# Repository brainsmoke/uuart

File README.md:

# Tiny USB-C to uart adapters using ch340n / ch340c / ch340b

* Green: simple 3v3 rx/tx (CH340N chip)
* Black: 3v3 rx/tx & reset circuit compatible with esptool (CH340C chip)
* Both: AP2112K-3.3 LDO

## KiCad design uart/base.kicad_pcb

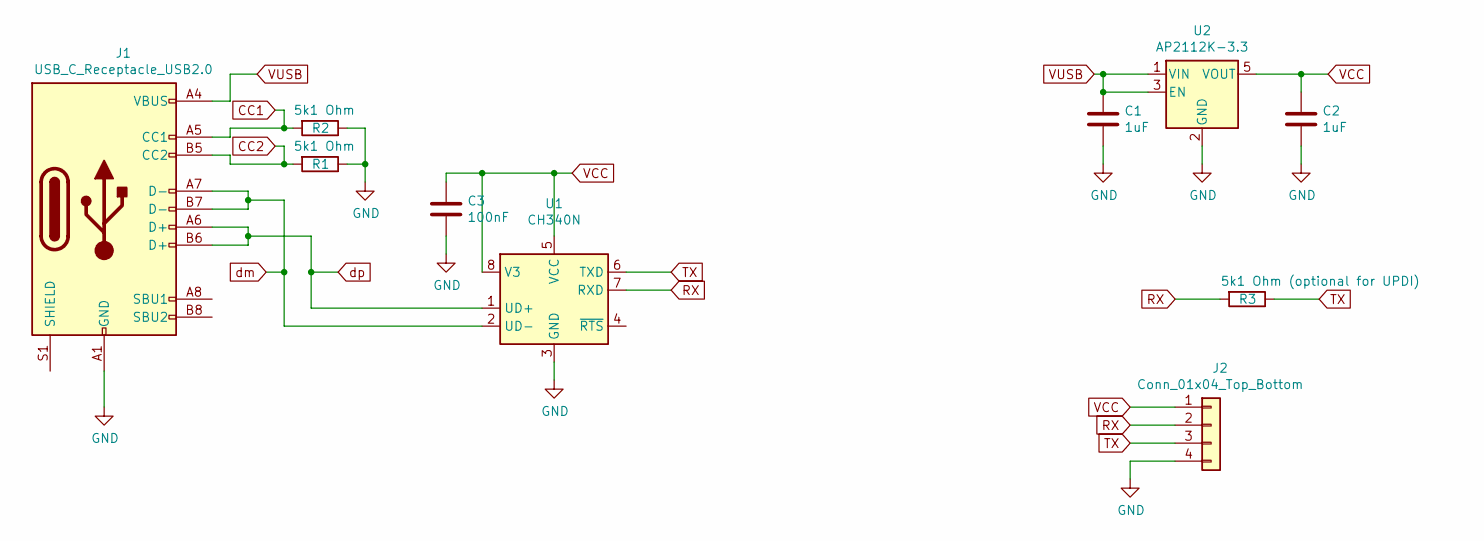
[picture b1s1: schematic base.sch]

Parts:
C1, C2: 1uF; C_0603_1608Metric
C3: 100nF; C_0603_1608Metric
J1: USB_C_Receptacle_USB2.0; USB_C_Receptacle_HRO_TYPE-C-31-M-12
J2: Conn_01x04_Top_Bottom; PinSocket_1x04_P2.54mm_Edge
R1, R2: 5k1 Ohm; R_0603_1608Metric
R3: 5k1 Ohm (optional for UPDI); R_0603_1608Metric
U1: CH340N; SOIC-8_3.9x4.9mm_P1.27mm
U2: AP2112K-3.3; SOT-23-5

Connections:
CC1: J1.A5 (CC1), R2.2
CC2: J1.B5 (CC2), R1.2
GND: C1.2, C2.2, C3.2, J1.A1 (GND), J1.A12 (GND), J1.B1 (GND), J1.B12 (GND), J2.4, R1.1, R2.1, U1.3 (GND), U2.2 (GND)
RX: J2.2, R3.2, U1.7 (RXD)
TX: J2.3, R3.1, U1.6 (TXD)
VCC: C2.1, C3.1, J2.1, U1.5 (VCC), U1.8 (V3), U2.5 (VOUT)
VUSB: C1.1, J1.A4 (VBUS), J1.A9 (VBUS), J1.B4 (VBUS), J1.B9 (VBUS), U2.1 (VIN), U2.3 (EN)
dm: J1.A7 (D-), J1.B7 (D-), U1.2 (UD-)
dp: J1.A6 (D+), J1.B6 (D+), U1.1 (UD+)

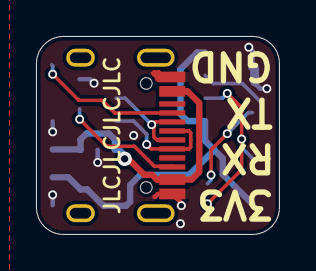
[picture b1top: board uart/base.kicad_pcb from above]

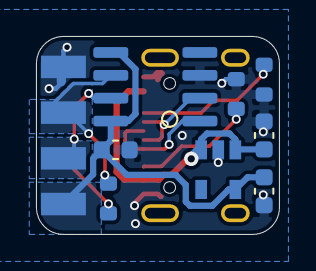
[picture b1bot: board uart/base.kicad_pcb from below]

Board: 2 copper layers, 13.5 x 11.0 mm, 10 parts (9 on the bottom side), 9 nets.

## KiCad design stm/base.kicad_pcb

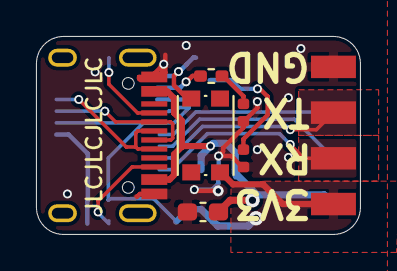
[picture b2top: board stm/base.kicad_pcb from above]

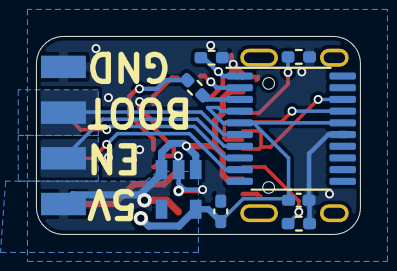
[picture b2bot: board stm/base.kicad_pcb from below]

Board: 2 copper layers, 18.0 x 11.0 mm, 15 parts (8 on the bottom side), 16 nets.

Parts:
C1: 1uF; C_0603_1608Metric_Pad1.08x0.95mm_HandSolder
C2, C3: 1uF; C_0402_1005Metric_Pad0.74x0.62mm_HandSolder
D1, D2: LED; LED_0402_1005Metric
J1: USB_C_Receptacle_USB2.0; USB_C_Receptacle_HRO_TYPE-C-31-M-12
J2: Conn_02x04_Top_Bottom; PinSocket_2x04_P2.54mm_Edge
R1, R2: 5k1 Ohm; R_0402_1005Metric_Pad0.72x0.64mm_HandSolder
R3, R4, R5: 10k Ohm; R_0402_1005Metric_Pad0.72x0.64mm_HandSolder
SW1: SW_SPST; SW_Push_1P1T_NO_CK_KMR2
U1: STM32F042F4Px; TSSOP-20_4.4x6.5mm_P0.65mm
U2: AP2112K-3.3; SOT-23-5

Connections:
CC1: J1.A5, R2.2
CC2: J1.B5, R1.2
EN: J2.6, U1.7
GND: C1.2, C2.2, C3.2, D1.1, D2.1, J1.A1, J1.A12, J1.B1, J1.B12, J2.4, J2.8, R1.1, R2.1, R4.2, U1.15, U2.2
unnamed: D1.2, R3.2
unnamed: D2.2, R5.2
unnamed: R4.1, SW1.1, U1.1
RST: J2.7, U1.6
RX: J2.2, U1.9
RXLED: R3.1, U1.3
TX: J2.3, U1.8
TXLED: R5.1, U1.2
VCC: C2.1, C3.1, J2.1, SW1.2, U1.4, U1.5, U1.16, U2.5
VUSB: C1.1, J1.A4, J1.A9, J1.B4, J1.B9, J2.5, U2.1, U2.3
dm: J1.A7, J1.B7, U1.17
dp: J1.A6, J1.B6, U1.18

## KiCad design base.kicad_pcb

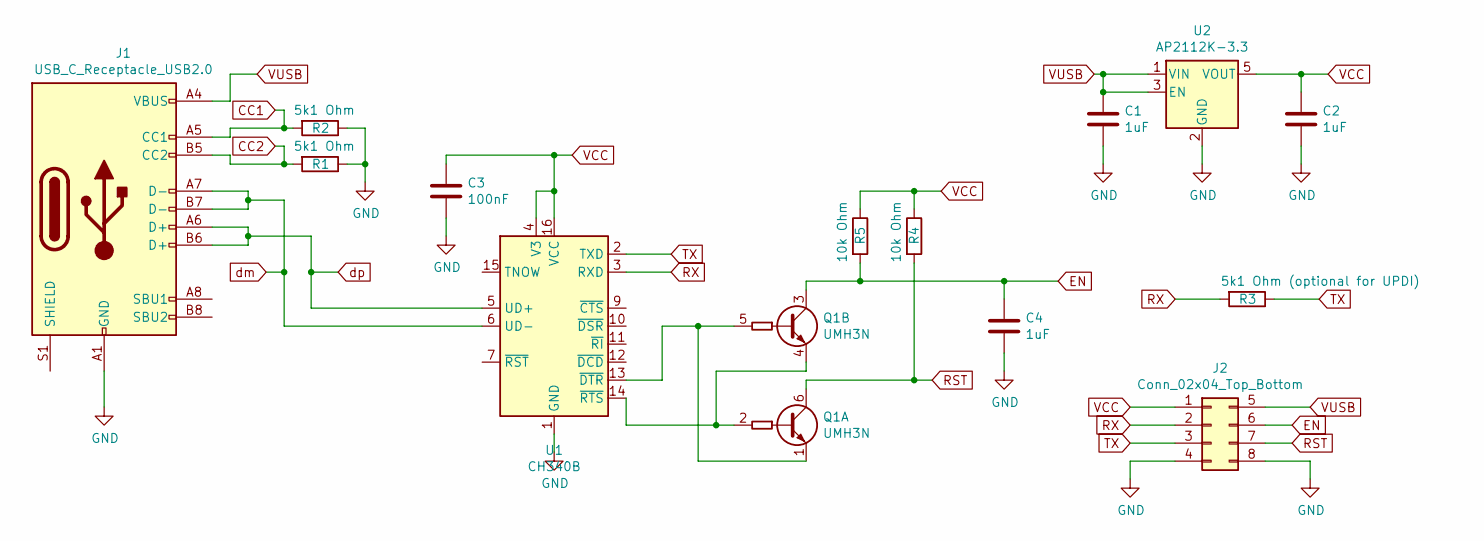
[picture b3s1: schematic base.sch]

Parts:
C1, C2, C4: 1uF; C_0603_1608Metric
C3: 100nF; C_0603_1608Metric
J1: USB_C_Receptacle_USB2.0; USB_C_Receptacle_HRO_TYPE-C-31-M-12
J2: Conn_02x04_Top_Bottom; PinSocket_2x04_P2.54mm_Edge
Q1: UMH3N; SOT-363_SC-70-6
R1, R2: 5k1 Ohm; R_0603_1608Metric
R3: 5k1 Ohm (optional for UPDI); R_0603_1608Metric
R4, R5: 10k Ohm; R_0603_1608Metric
U1: CH340B; SOIC-16_3.9x9.9mm_P1.27mm
U2: AP2112K-3.3; SOT-23-5

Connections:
CC1: J1.A5 (CC1), R2.2
CC2: J1.B5 (CC2), R1.2
EN: C4.1, J2.6, Q1.3 (C2), R5.2
GND: C1.2, C2.2, C3.2, C4.2, J1.A1 (GND), J1.A12 (GND), J1.B1 (GND), J1.B12 (GND), J2.4, J2.8, R1.1, R2.1, U1.1 (GND), U2.2 (GND)
unnamed: Q1.1 (E1), Q1.5 (B2), U1.13 (~DTR)
unnamed: Q1.2 (B1), Q1.4 (E2), U1.14 (~RTS)
RST: J2.7, Q1.6 (C1), R4.2
RX: J2.2, R3.2, U1.3 (RXD)
TX: J2.3, R3.1, U1.2 (TXD)
VCC: C2.1, C3.1, J2.1, R4.1, R5.1, U1.4 (V3), U1.16 (VCC), U2.5 (VOUT)
VUSB: C1.1, J1.A4 (VBUS), J1.A9 (VBUS), J1.B4 (VBUS), J1.B9 (VBUS), J2.5, U2.1 (VIN), U2.3 (EN)
dm: J1.A7 (D-), J1.B7 (D-), U1.6 (UD-)
dp: J1.A6 (D+), J1.B6 (D+), U1.5 (UD+)

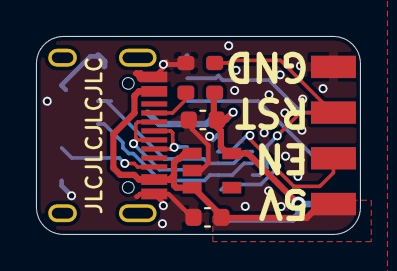
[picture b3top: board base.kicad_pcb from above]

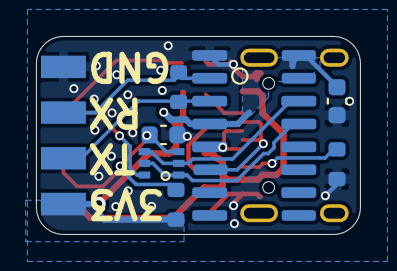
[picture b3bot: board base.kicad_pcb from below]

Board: 2 copper layers, 18.0 x 11.0 mm, 14 parts (8 on the bottom side), 13 nets.

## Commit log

2023-05-12 small tweak
2023-05-12 add uart-only PCB
2023-06-06 latest version
2023-06-06 readme
2023-06-06 filename typo
2023-06-10 small readme edit
2024-01-14 rx/tx mislabeling, (oops :-E)
2024-01-14 add stm32f042 based board
2024-03-11 stm32f0x2 based usb-cdc boards
